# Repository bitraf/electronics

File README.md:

# Bitraf Electronics Library (BEL)

This repository has a list of components available at Bitraf, 
all components are free to use for members. 
We strive to have the list of components found here available 
at all times, so members can use them in new designs.  

There is also a list of referece designs made in KiCad, such as step down converter, 
hello world blinky led based on STM32 uC, a USB hub etc. These are meant to be used 
as building blocks for ne designs for both members and others. 

For B-Timer, see _/Reference-designs/stm32f070/B-timer_.

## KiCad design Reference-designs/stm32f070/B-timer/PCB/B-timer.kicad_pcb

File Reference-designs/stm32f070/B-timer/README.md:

# B-Timer with STM32F070(C6)

## Making the board
The _/PCB_ directory contains KiCad files for reference. See _.pro_ or _.sch_ and _.kicad_pcb_ as starting points.

You can easily generate a _.pos_ file for use with the pick-and-place machine:

1. In the _.kicad_pcb_ file, set the "auxiliary axis origin" (_Place > Drill and Place Offset_). This point should be at the exact top left corner of the board edge, which by default shows as a thick yellow line on the "Edge.Cuts" layer.
2. Export by going to _File > Fabrication Outputs > Footprint Position (.pos) File_.

You can choose to mount the LED's in whichever direction you choose (up or down), but make sure to adjust the code accordingly. See the following section for more details.

## Flashing the board
You will need a programmer like the _ST-Link V2_ to (easily) flash your board. Make sure you connect the four pins (GND, VCC, SWDIO, SWCLK) properly.

The _/Software_ directory contains the files needed to flash your board with basic timer functionality. Assuming you are using Linux or a similar OS, the steps are:

1. Navigate to _/Software_.
1. Run `make` to compile the code.
1. Run `flash` to send it to the board.
1. If the board shows digits as expected, congrats! If it shows gibberish, check the `set_led` function in _/Software/Src/main.c_ and comment/uncomment the relevant lines (search for `@IMPORTANT`) depending on the orientation of your LED's. Remember to compile before you flash again. Lastly, if nothing shows up or something is not behaving properly, remember that the issue may be with the hardware (poorly connected pins, misaligned components, etc.).

Notes:
1. This particular implementation of `flash` in the Makefile uses `st-link`/`st-flash`. You can follow these steps ([A](https://www.youtube.com/watch?v=5nr_3o7D1To), [B](https://www.youtube.com/watch?v=pHyz2-wbDw4)) for how to install it. Alternatively, you can use `openocd` or any other software compatible with ARM chips (i.e. `avrdude` is _not_ compatible with ARM).
2. _/PCB/Software_ (not the same directory as _/Software_) contains scripts to generate digits for the display. You can safely ignore it if you are still getting familiar with this project.

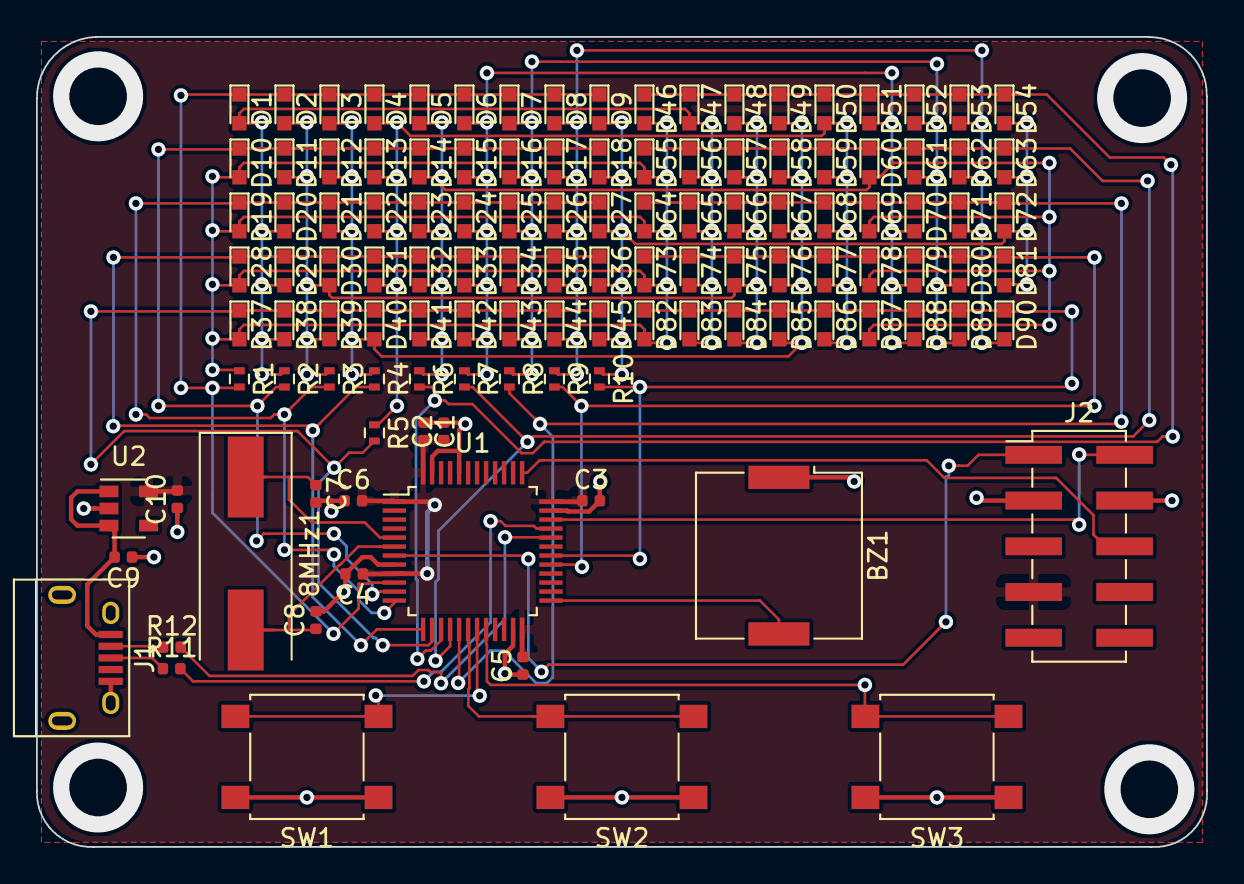
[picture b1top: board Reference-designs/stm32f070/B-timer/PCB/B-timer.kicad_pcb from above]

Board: 2 copper layers, 65.0 x 45.0 mm, 121 parts (0 on the bottom side), 36 nets.

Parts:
8MHz1: Crystal; Crystal_SMD_HC49-SD
BZ1: Buzzer; Buzzer_Murata_PKMCS0909E4000-R1
C1, C3, C4, C5, C6, C10: 0.1µF; C_0402_1005Metric
C2, C9: 1µF; C_0402_1005Metric
C7, C8: 18pF; C_0402_1005Metric
D1, D2, D3, D4, D5, D6, D7, D8, D9, D10, D11, D12, D13, D14, D15, D16, D17, D18, D19, D20, D21, D22, D23, D24, D25, D26, D27, D28, D29, D30, D31, D32, D33, D34, D35, D36, D37, D38, D39, D40, D41, D42, D43, D44, D45, D46, D47, D48, D49, D50, D51, D52, D53, D54, D55, D56, D57, D58, D59, D60, D61, D62, D63, D64, D65, D66, D67, D68, D69, D70, D71, D72, D73, D74, D75, D76, D77, D78, D79, D80, D81, D82, D83, D84, D85, D86, D87, D88, D89, D90: LED; LED_0603
J1: USB_B_Micro; USB_Micro-B
J2: Conn_02x05_Odd_Even; PinHeader_2x05_P2.54mm_Vertical_SMD
R1, R2, R3, R4, R5, R6, R7, R8, R9, R10: 68R; R_0402
R11, R12: 22R; R_0402_1005Metric
SW1, SW2, SW3: SW_Push; SW_SPST_B3S-1000
U1: STM32F070C6Tx; LQFP-48_7x7mm_P0.5mm
U2: MIC5504-3.3YM5; SOT-23-5

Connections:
+3V3: C1.2, C2.1, C3.1, C4.1, C5.2, C6.2, C10.2, J2.7, U1.1, U1.9, U1.24, U1.36, U1.48, U2.5
+5V: C9.2, J1.1, U2.1, U2.3
/D+: R11.2, U1.33
/D-: R12.2, U1.32
/NRST: J2.1, U1.7
/SWCLK: J2.6, U1.37
/SWDIO: J2.2, U1.34
D0: D1.1, D2.1, D3.1, D4.1, D5.1, D6.1, D7.1, D8.1, D9.1, R1.2, U1.10
D1: D10.1, D11.1, D12.1, D13.1, D14.1, D15.1, D16.1, D17.1, D18.1, R2.2, U1.11
D2: D19.1, D20.1, D21.1, D22.1, D23.1, D24.1, D25.1, D26.1, D27.1, R3.2, U1.12
D3: D28.1, D29.1, D30.1, D31.1, D32.1, D33.1, D34.1, D35.1, D36.1, R4.2, U1.13
D4: D37.1, D38.1, D39.1, D40.1, D41.1, D42.1, D43.1, D44.1, D45.1, R5.2, U1.14
D5: D46.1, D47.1, D48.1, D49.1, D50.1, D51.1, D52.1, D53.1, D54.1, R6.2, U1.15
D6: D55.1, D56.1, D57.1, D58.1, D59.1, D60.1, D61.1, D62.1, D63.1, R7.2, U1.16
D7: D64.1, D65.1, D66.1, D67.1, D68.1, D69.1, D70.1, D71.1, D72.1, R8.2, U1.17
D8: D73.1, D74.1, D75.1, D76.1, D77.1, D78.1, D79.1, D80.1, D81.1, R9.2, U1.29
D9: D82.1, D83.1, D84.1, D85.1, D86.1, D87.1, D88.1, D89.1, D90.1, R10.2, U1.30
GND: BZ1.1, C1.1, C2.2, C3.2, C4.2, C5.1, C6.1, C7.2, C8.2, C9.1, C10.1, J1.5, J1.6, J2.3, J2.4, SW1.1, SW2.1, SW3.1, U1.8, U1.23, U1.35, U1.44, U1.47, U2.2
unnamed: 8MHz1.1, C7.1, U1.5
unnamed: 8MHz1.2, C8.1, U1.6
unnamed: BZ1.2, U1.25
unnamed: D1.2, D20.2, D29.2, D38.2, D47.2, D56.2, D65.2, D74.2, D83.2, R2.1
unnamed: D10.2, D19.2, D28.2, D37.2, D46.2, D55.2, D64.2, D73.2, D82.2, R1.1
unnamed: D2.2, D11.2, D30.2, D39.2, D48.2, D57.2, D66.2, D75.2, D84.2, R3.1
unnamed: D3.2, D12.2, D21.2, D40.2, D49.2, D58.2, D67.2, D76.2, D85.2, R4.1
unnamed: D4.2, D13.2, D22.2, D31.2, D50.2, D59.2, D68.2, D77.2, D86.2, R5.1
unnamed: D5.2, D14.2, D23.2, D32.2, D41.2, D60.2, D69.2, D78.2, D87.2, R6.1
unnamed: D6.2, D15.2, D24.2, D33.2, D42.2, D51.2, D70.2, D79.2, D88.2, R7.1
unnamed: D7.2, D16.2, D25.2, D34.2, D43.2, D52.2, D61.2, D80.2, D89.2, R8.1
unnamed: D8.2, D17.2, D26.2, D35.2, D44.2, D53.2, D62.2, D71.2, D90.2, R9.1
unnamed: D9.2, D18.2, D27.2, D36.2, D45.2, D54.2, D63.2, D72.2, D81.2, R10.1
unnamed: J1.2, R12.1
unnamed: J1.3, R11.1
unnamed: SW1.2, U1.19
unnamed: SW2.2, U1.18
unnamed: SW3.2, U1.20

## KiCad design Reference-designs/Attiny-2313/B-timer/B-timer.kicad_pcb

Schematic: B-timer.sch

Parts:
BZ1: Buzzer; Buzzer_Murata_PKMCS0909E4000-R1; MPN PKMCS0909E4000-R1
C1: 0.1µF; C_0402
C2: 1µF; C_0402
D1, D2, D3, D4, D5, D6, D7, D8, D9, D10, D11, D12, D13, D14, D15, D16, D17, D18, D19, D20, D21, D22, D23, D24, D25, D26, D27, D28, D29, D30, D31, D32, D33, D34, D35, D36, D37, D38, D39, D40, D41, D42, D43, D44, D45, D46, D47, D48, D49, D50, D51, D52, D53, D54, D55, D56, D57, D58, D59, D60, D61, D62, D63, D64, D65, D66, D67, D68, D69, D70, D71, D72, D73, D74, D75, D76, D77, D78, D79, D80, D81, D82, D83, D84, D85, D86, D87, D88, D89, D90: LED; LED_0603
J1: USB_B_Micro; USB_Micro-B
J2: Conn_02x03_Odd_Even; Pin_Header_Straight_2x03_Pitch2.54mm_SMD
R1, R2, R3, R4, R5, R6, R7, R8, R9, R10: R; R_0402
SW1, SW3: SW_Push; SW_SPST_B3S-1000; MPN PTS645SM43SMTR92 LFS
SW2: SW_Push; SW_SPST_B3S-1000; MPN PTS645SM43SMTR92LFS
U1: ATTINY2313-20MU; VQFN20-SMALL

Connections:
+5V: C1.1, C2.1, J1.1, J2.2, U1.18 (VCC)
D0: D1.1, D2.1, D3.1, D4.1, D5.1, D6.1, D7.1, D8.1, D9.1, R1.2, U1.20 (PD0)
D1: D10.1, D11.1, D12.1, D13.1, D14.1, D15.1, D16.1, D17.1, D18.1, R2.2, U1.1 (PD1)
D2: D19.1, D20.1, D21.1, D22.1, D23.1, D24.1, D25.1, D26.1, D27.1, R3.2, U1.4 (PD2)
D3: D28.1, D29.1, D30.1, D31.1, D32.1, D33.1, D34.1, D35.1, D36.1, R4.2, U1.5 (PD3)
D4: D37.1, D38.1, D39.1, D40.1, D41.1, D42.1, D43.1, D44.1, D45.1, R5.2, U1.6 (PD4)
D5: D46.1, D47.1, D48.1, D49.1, D50.1, D51.1, D52.1, D53.1, D54.1, R6.2, U1.7 (PD5)
D6: D55.1, D56.1, D57.1, D58.1, D59.1, D60.1, D61.1, D62.1, D63.1, R7.2, U1.9 (PD6)
D7: D64.1, D65.1, D66.1, D67.1, D68.1, D69.1, D70.1, D71.1, D72.1, R8.2, U1.10 (PB0)
D8: D73.1, D74.1, D75.1, D76.1, D77.1, D78.1, D79.1, D80.1, D81.1, R9.2, U1.11 (PB1)
D9: D82.1, D83.1, D84.1, D85.1, D86.1, D87.1, D88.1, D89.1, D90.1, R10.2, U1.12 (PB2)
GND: BZ1.2, C1.2, C2.2, J1.5, J1.6, J2.6, SW1.1, SW2.1, SW3.1, U1.8 (GND), U1.21 (GND)
MISO: J2.1, U1.16 (PB6)
MOSI: J2.4, U1.15 (PB5)
unnamed: BZ1.1, U1.14 (PB4)
unnamed: D1.2, D20.2, D29.2, D38.2, D47.2, D56.2, D65.2, D74.2, D83.2, R2.1
unnamed: D10.2, D19.2, D28.2, D37.2, D46.2, D55.2, D64.2, D73.2, D82.2, R1.1
unnamed: D2.2, D11.2, D30.2, D39.2, D48.2, D57.2, D66.2, D75.2, D84.2, R3.1
unnamed: D3.2, D12.2, D21.2, D40.2, D49.2, D58.2, D67.2, D76.2, D85.2, R4.1
unnamed: D4.2, D13.2, D22.2, D31.2, D50.2, D59.2, D68.2, D77.2, D86.2, R5.1
unnamed: D5.2, D14.2, D23.2, D32.2, D41.2, D60.2, D69.2, D78.2, D87.2, R6.1
unnamed: D6.2, D15.2, D24.2, D33.2, D42.2, D51.2, D70.2, D79.2, D88.2, R7.1
unnamed: D7.2, D16.2, D25.2, D34.2, D43.2, D52.2, D61.2, D80.2, D89.2, R8.1
unnamed: D8.2, D17.2, D26.2, D35.2, D44.2, D53.2, D62.2, D71.2, D90.2, R9.1
unnamed: D9.2, D18.2, D27.2, D36.2, D45.2, D54.2, D63.2, D72.2, D81.2, R10.1
unnamed: SW1.2, U1.2 (PA1/XTAL2)
unnamed: SW2.2, U1.3 (PA0/XTAL1)
unnamed: SW3.2, U1.13 (PB3)
RESET: J2.5, U1.19 (PA2/~RESET)
SCK: J2.3, U1.17 (PB7)

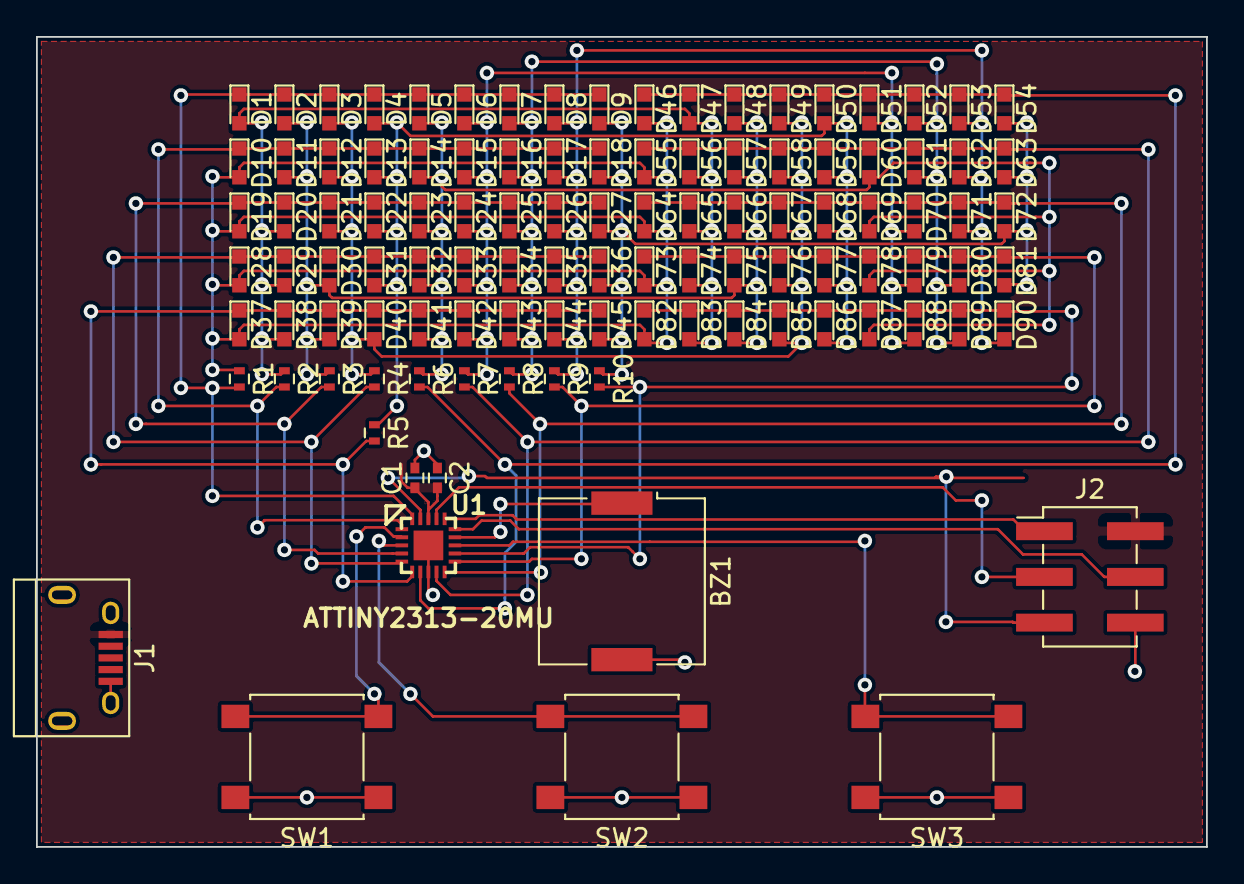
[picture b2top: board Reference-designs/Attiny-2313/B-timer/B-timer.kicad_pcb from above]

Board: 2 copper layers, 65.0 x 45.0 mm, 109 parts (0 on the bottom side), 30 nets.

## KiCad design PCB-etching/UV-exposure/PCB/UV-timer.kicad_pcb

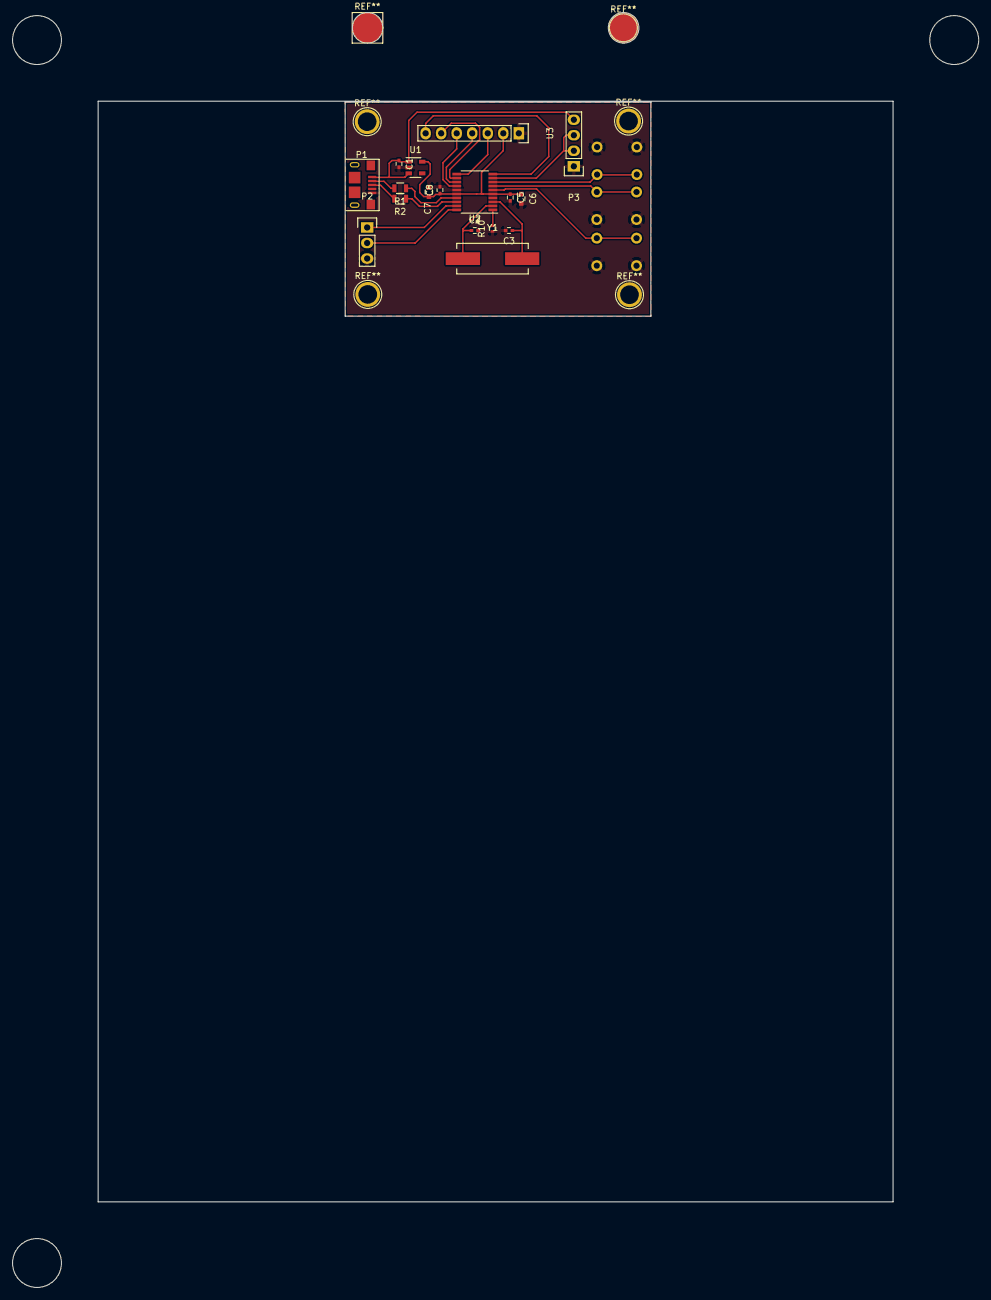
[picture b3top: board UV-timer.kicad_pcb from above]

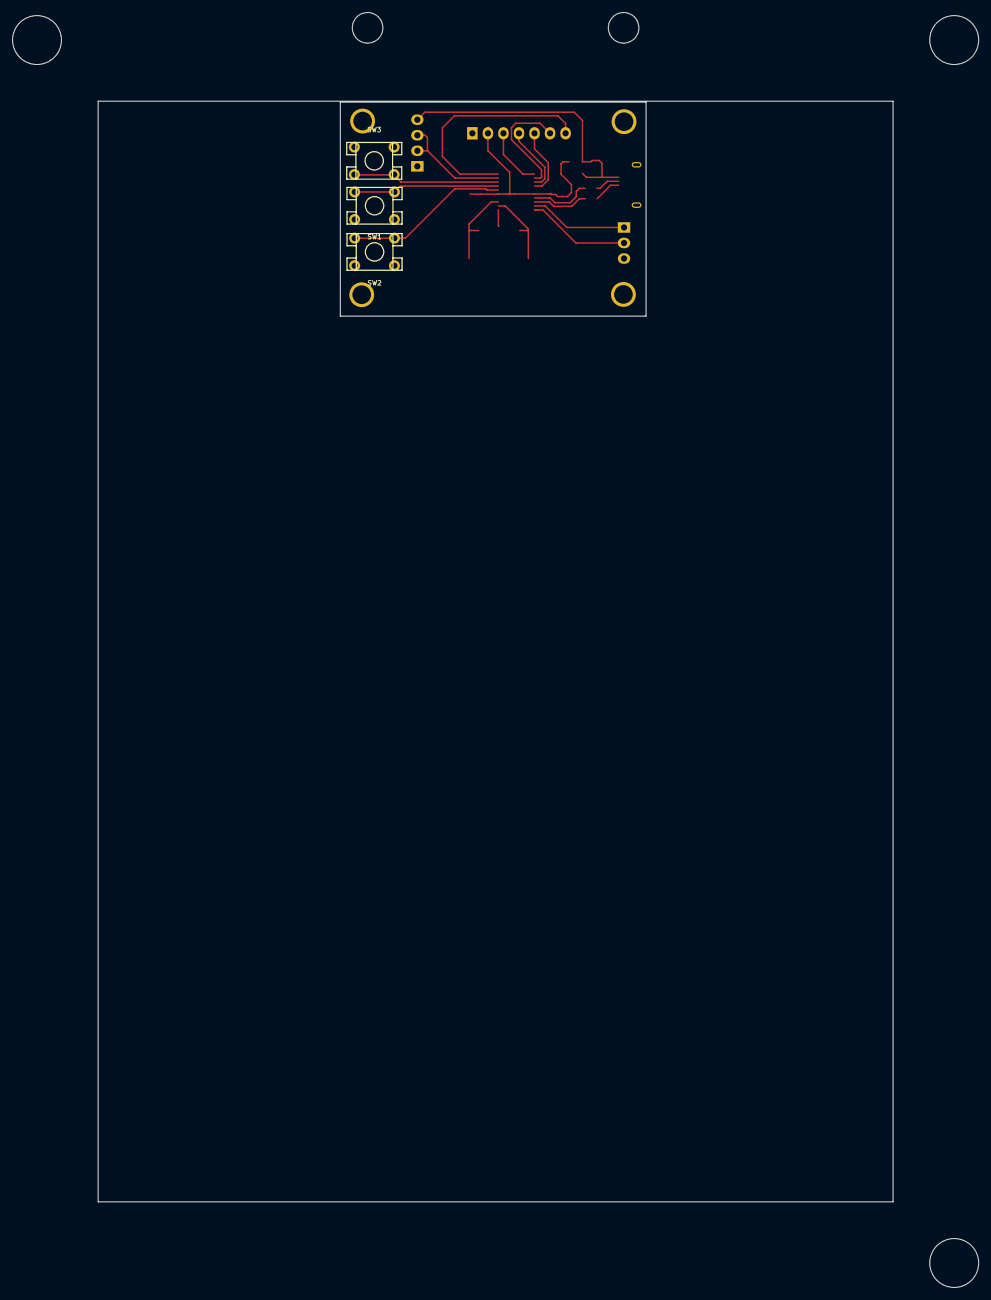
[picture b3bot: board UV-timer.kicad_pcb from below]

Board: 2 copper layers, 130.0 x 180.0 mm, 20 parts (3 on the bottom side), 21 nets.

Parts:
C1, C5, C8: 0.1uF; C_0402
C2, C3: 18pF; C_0402
C6, C7: 4.7uF; C_0603
P1: USB_OTG; FCI_10118193-0001LF
P2: CONN_01X03; Pin_Header_Straight_1x03
P3: CONN_01X04; Pin_Header_Straight_1x04
R1, R2: 22R; R_0805
R10: 0R; R_0402
SW1, SW2, SW3: SW_Push; SPST-4-PIN_6mm_thru
U1: TC2EF; SOT-23-5
U2: STM32F070; TSSOP-20_4.4x6.5mm_Pitch0.65mm
U3: OLED; Pin_Header_Straight_1x07
Y1: 8MHz; Crystal_HC49-SD_SMD

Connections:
+3V3: C5.1, C6.1, C7.1, C8.1, U1.5, U2.5, U2.16, U3.2
+5V: C1.1, P1.1, P3.4, U1.1, U1.3
GND: C1.2, C2.2, C3.2, C5.2, C6.2, C7.2, C8.2, P1.5, P2.3, P3.1, R10.1, SW1.1, SW2.1, SW3.1, U1.2, U2.15, U3.1
unnamed: C2.1, U2.2, Y1.1
unnamed: C3.1, U2.3, Y1.2
unnamed: P1.2, R1.2
unnamed: P1.3, R2.2
unnamed: R10.2, U2.1
unnamed: SW1.2, U2.7
unnamed: SW2.2, U2.6
unnamed: SW3.2, U2.8
unnamed: U2.10, U3.7
unnamed: U2.11, U3.3
unnamed: U2.12, U3.6
unnamed: U2.13, U3.4
unnamed: U2.14, U3.5
REL_1: P3.2, P3.3, U2.9
SWCLK: P2.2, U2.20
SWDIO: P2.1, U2.19
USB_DM: R1.1, U2.17
USB_DP: R2.1, U2.18

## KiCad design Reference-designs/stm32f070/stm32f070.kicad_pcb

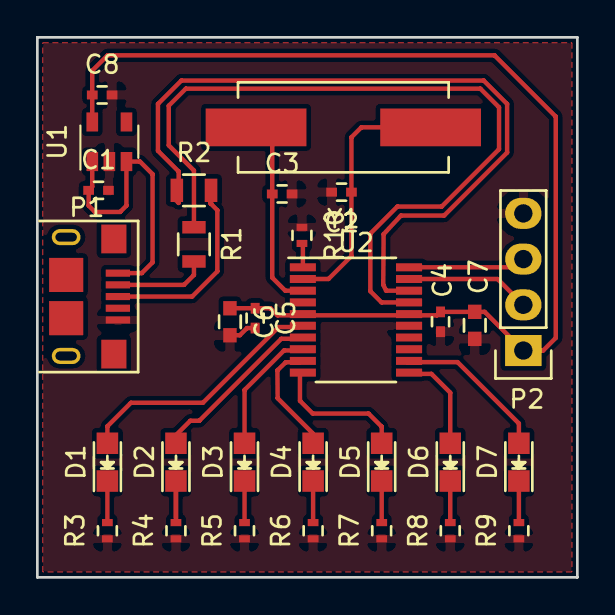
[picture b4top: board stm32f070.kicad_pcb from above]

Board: 2 copper layers, 30.0 x 30.0 mm, 30 parts (0 on the bottom side), 26 nets.

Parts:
C1, C4, C5, C8: 0.1uF; C_0402
C2, C3: 18pF; C_0402
C6, C7: 4.7uF; C_0603
D1, D2, D3, D4, D5, D6, D7: LED; LED_0805
P1: USB_OTG; FCI_10118193-0001LF
P2: CONN_01X04; Pin_Header_Straight_1x04
R1, R2: 22R; R_0805
R3, R4, R5, R6, R7, R8, R9: 220R; R_0402
R10: 0R; R_0402
U1: TC2EF; SOT-23-5
U2: STM32F070; TSSOP-20_4.4x6.5mm_Pitch0.65mm
Y1: 8MHz; Crystal_HC49-SD_SMD

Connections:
+3V3: C4.1, C5.1, C6.1, C7.1, C8.1, P2.1, U1.5, U2.5, U2.16
+5V: C1.1, P1.1, U1.1, U1.3
/PA0: D1.2, U2.6
/PA1: D2.2, U2.7
/PA2: D3.2, U2.8
/PA3: D4.2, U2.9
/PA4: D5.2, U2.10
/PA5: D6.2, U2.11
/PA6: D7.2, U2.12
GND: C1.2, C2.2, C3.2, C4.2, C5.2, C6.2, C7.2, C8.2, P1.5, P2.4, R3.1, R4.1, R5.1, R6.1, R7.1, R8.1, R9.1, R10.1, U1.2, U2.15
unnamed: C2.1, U2.2, Y1.1
unnamed: C3.1, U2.3, Y1.2
unnamed: D1.1, R3.2
unnamed: D2.1, R4.2
unnamed: D3.1, R5.2
unnamed: D4.1, R6.2
unnamed: D5.1, R7.2
unnamed: D6.1, R8.2
unnamed: D7.1, R9.2
unnamed: P1.2, R1.2
unnamed: P1.3, R2.2
unnamed: R10.2, U2.1
SWCLK: P2.3, U2.20
SWDIO: P2.2, U2.19
USB_DM: R1.1, U2.17
USB_DP: R2.1, U2.18

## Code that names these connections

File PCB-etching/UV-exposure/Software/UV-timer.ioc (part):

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Mcu.Name=STM32F070F6Px
Mcu.Package=TSSOP20
Mcu.UserName=STM32F070F6Px
PA0.GPIOParameters=GPIO_PuPd,GPIO_Label,GPIO_ModeDefaultEXTI
PA0.GPIO_Label=BUT_0
PA0.GPIO_ModeDefaultEXTI=GPIO_MODE_IT_RISING
PA0.GPIO_PuPd=GPIO_PULLUP
PA0.Signal=GPXTI0
PA1.GPIOParameters=GPIO_PuPd,GPIO_Label
PA1.GPIO_Label=BUT_1
PA1.GPIO_PuPd=GPIO_PULLUP
PA1.Signal=GPXTI1
PA11.Mode=Device
PA11.Signal=USB_DM
PA12.Mode=Device
PA12.Signal=USB_DP
PA13.Mode=Serial_Wire
PA13.Signal=SYS_SWDIO
PA14.Mode=Serial_Wire
PA14.Signal=SYS_SWCLK
PA2.GPIOParameters=GPIO_PuPd,GPIO_Label
PA2.GPIO_Label=BUT_2
PA2.GPIO_PuPd=GPIO_PULLUP
PA2.Signal=GPXTI2
PA3.GPIOParameters=GPIO_Label
PA3.GPIO_Label=REL_1
PA3.Signal=GPIO_Output
PA4.Mode=NSS_Signal_Hard_Output
PA4.Signal=SPI1_NSS
PA5.Mode=Simplex_Bidirectional_Master
PA5.Signal=SPI1_SCK
PA7.Mode=Simplex_Bidirectional_Master
PA7.Signal=SPI1_MOSI
PB1.GPIOParameters=GPIO_Label
PB1.GPIO_Label=RES
PB1.Signal=GPIO_Output
PF0-OSC_IN.Mode=HSE-External-Oscillator
PF0-OSC_IN.Signal=RCC_OSC_IN
PF1-OSC_OUT.Mode=HSE-External-Oscillator
PF1-OSC_OUT.Signal=RCC_OSC_OUT
RCC.SYSCLKFreq_VALUE=48000000
RCC.SYSCLKSource=RCC_SYSCLKSOURCE_PLLCLK
board=UV-timer

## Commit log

2018-01-29 Updated the Readme
2018-01-31 o Adding etching jig.
2018-01-31 Updated UV exposure jig
2018-01-31 Changed name of exposure jig, added the etching tank freecad file
2018-01-31 Added a reference deisgn based on STM32F070
2018-02-05 Clean up of PCB etching stuff and added software for the timer.
2018-02-06 Updated the timer to user minutes and seconds
2018-10-09 Added an attiny referece design
2018-10-09 Added a Bitraf library
2018-10-09 Update version
2018-10-09 First version layout
2018-10-16 Last update Oyvind
2018-10-23 First version of software, just showing numbers
2018-10-23 Simple countdown, added Freecad cover file
2018-10-24 Code too big, needs optimization
2018-10-24 Cleaned up Oyvinds mess. Added double buffering. Works OK, but start is slow for some reason
2018-10-24 b-timer: ignore build outputs
2018-10-24 b-timer: ignore sym-lib-table
2019-02-22 Added a B-timer based on STM32
2019-03-05 Generated code for B-timer V2
2019-03-06 First LED-code
2019-03-15 Display and buttons working. No functionality just yet though.
2019-03-15 Basic timer function
2019-11-01 Added README.md for b-timer
2019-11-01 Adjusted 68R and 18pF values and regenerated kicad_pcb file
2019-11-19 Added 'flash' to Makefile
2019-11-19 Added comments in main.c to help out with LED orientation
2019-11-19 Moved README.md to the project's main directory and fleshed it out
2019-11-19 Added a tiny note in the main README.md to point to the project's folders
2019-11-19 Removed outdated KiCad files in favor of those in the PCB folder
